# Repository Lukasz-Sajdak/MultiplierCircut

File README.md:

# Multiplier Circuit

## Overview
Analog multiplier circuit designed to perform multiplication of two input signals by utilizing various functional blocks working in tandem. The circuit uses customized components for efficient operation and to meet specific design requirements.

## Main Functional Blocks
The schematic is divided into the following key sections:

### Power Supply
- **Purpose:** Voltage stabilization for the circuit.
- **Components:**
  - **V+ Regulation:** The circuit uses a standard power supply for V+.
  - **V- Generation:** The negative voltage is generated using the **ICL7660AIBAZA** charge pump.

### Charge Pump
- **Purpose:** Generates the negative voltage required for specific circuit components.

### Voltage-Frequency Converter
- **Purpose:** This block, based on the **LM331**, controls and filters the input signal.
- **Adjustment:** The signal can be adjusted using an **R3 potentiometer** for finer control over the frequency.
- **Issue:** The V/F Converter isn't operating as expected due to incorrect resistor choices and insufficient current flowing into the IC.

### Adding Offset
- **Purpose:** Adds a frequency shift to the input signal, ensuring correct operation when dealing with a 0V input.
- **Components:** Implemented with the **TS912** operational amplifier.

### Subtracting Offset
- **Purpose:** Compensates for any voltage offset by subtracting a specific value.
- **Components:** The **TS912** operational amplifier is used here as well, with the offset adjusted via the **R18 potentiometer**.

### Voltage Reference
- **Purpose:** Provides a reference voltage for the circuit.
- **Component:** **TL431BIDBZR** is used for this purpose.

### Analog Switch
- **Component:** **DG419DY**  
- **Purpose:** Transfers charge based on V/F signal to perform multiplication with Vy. Connected to capacitor and output stage.

## How It Works

The circuit receives two input signals: **Vx** and **Vy**, and performs an analog multiplication of these signals.

The **Vx** signal is fed into a voltage-to-frequency converter (**V/F**, based on LM331), which converts the voltage into a frequency proportional to **Vx**. This frequency output is then used to control an analog switch.

The analog switch operates by transferring charge from the **Vy** signal to a capacitor in response to the frequency generated by the V/F converter.

**Switch connections:**
- **IN** — control signal from V/F (frequency depends on **Vx**)  
- **S2** — voltage input **Vy**  
- **D** — capacitor  
- **S1** — output  

As a result, the amount of transferred charge—and thus the output voltage—depends on both the **Vy** amplitude and the frequency determined by **Vx**. This results in **analog multiplication** of **Vx** and **Vy**.

## Known Issues
- The **V/F** is not functioning correctly due to improper resistor selection and insufficient current flow to the integrated circuit. This needs to be addressed for proper operation.

## PCB Design
The physical implementation of the circuit has been designed using **KiCad EDA 8.0.2** software.

The circuit has been **soldered and assembled**.

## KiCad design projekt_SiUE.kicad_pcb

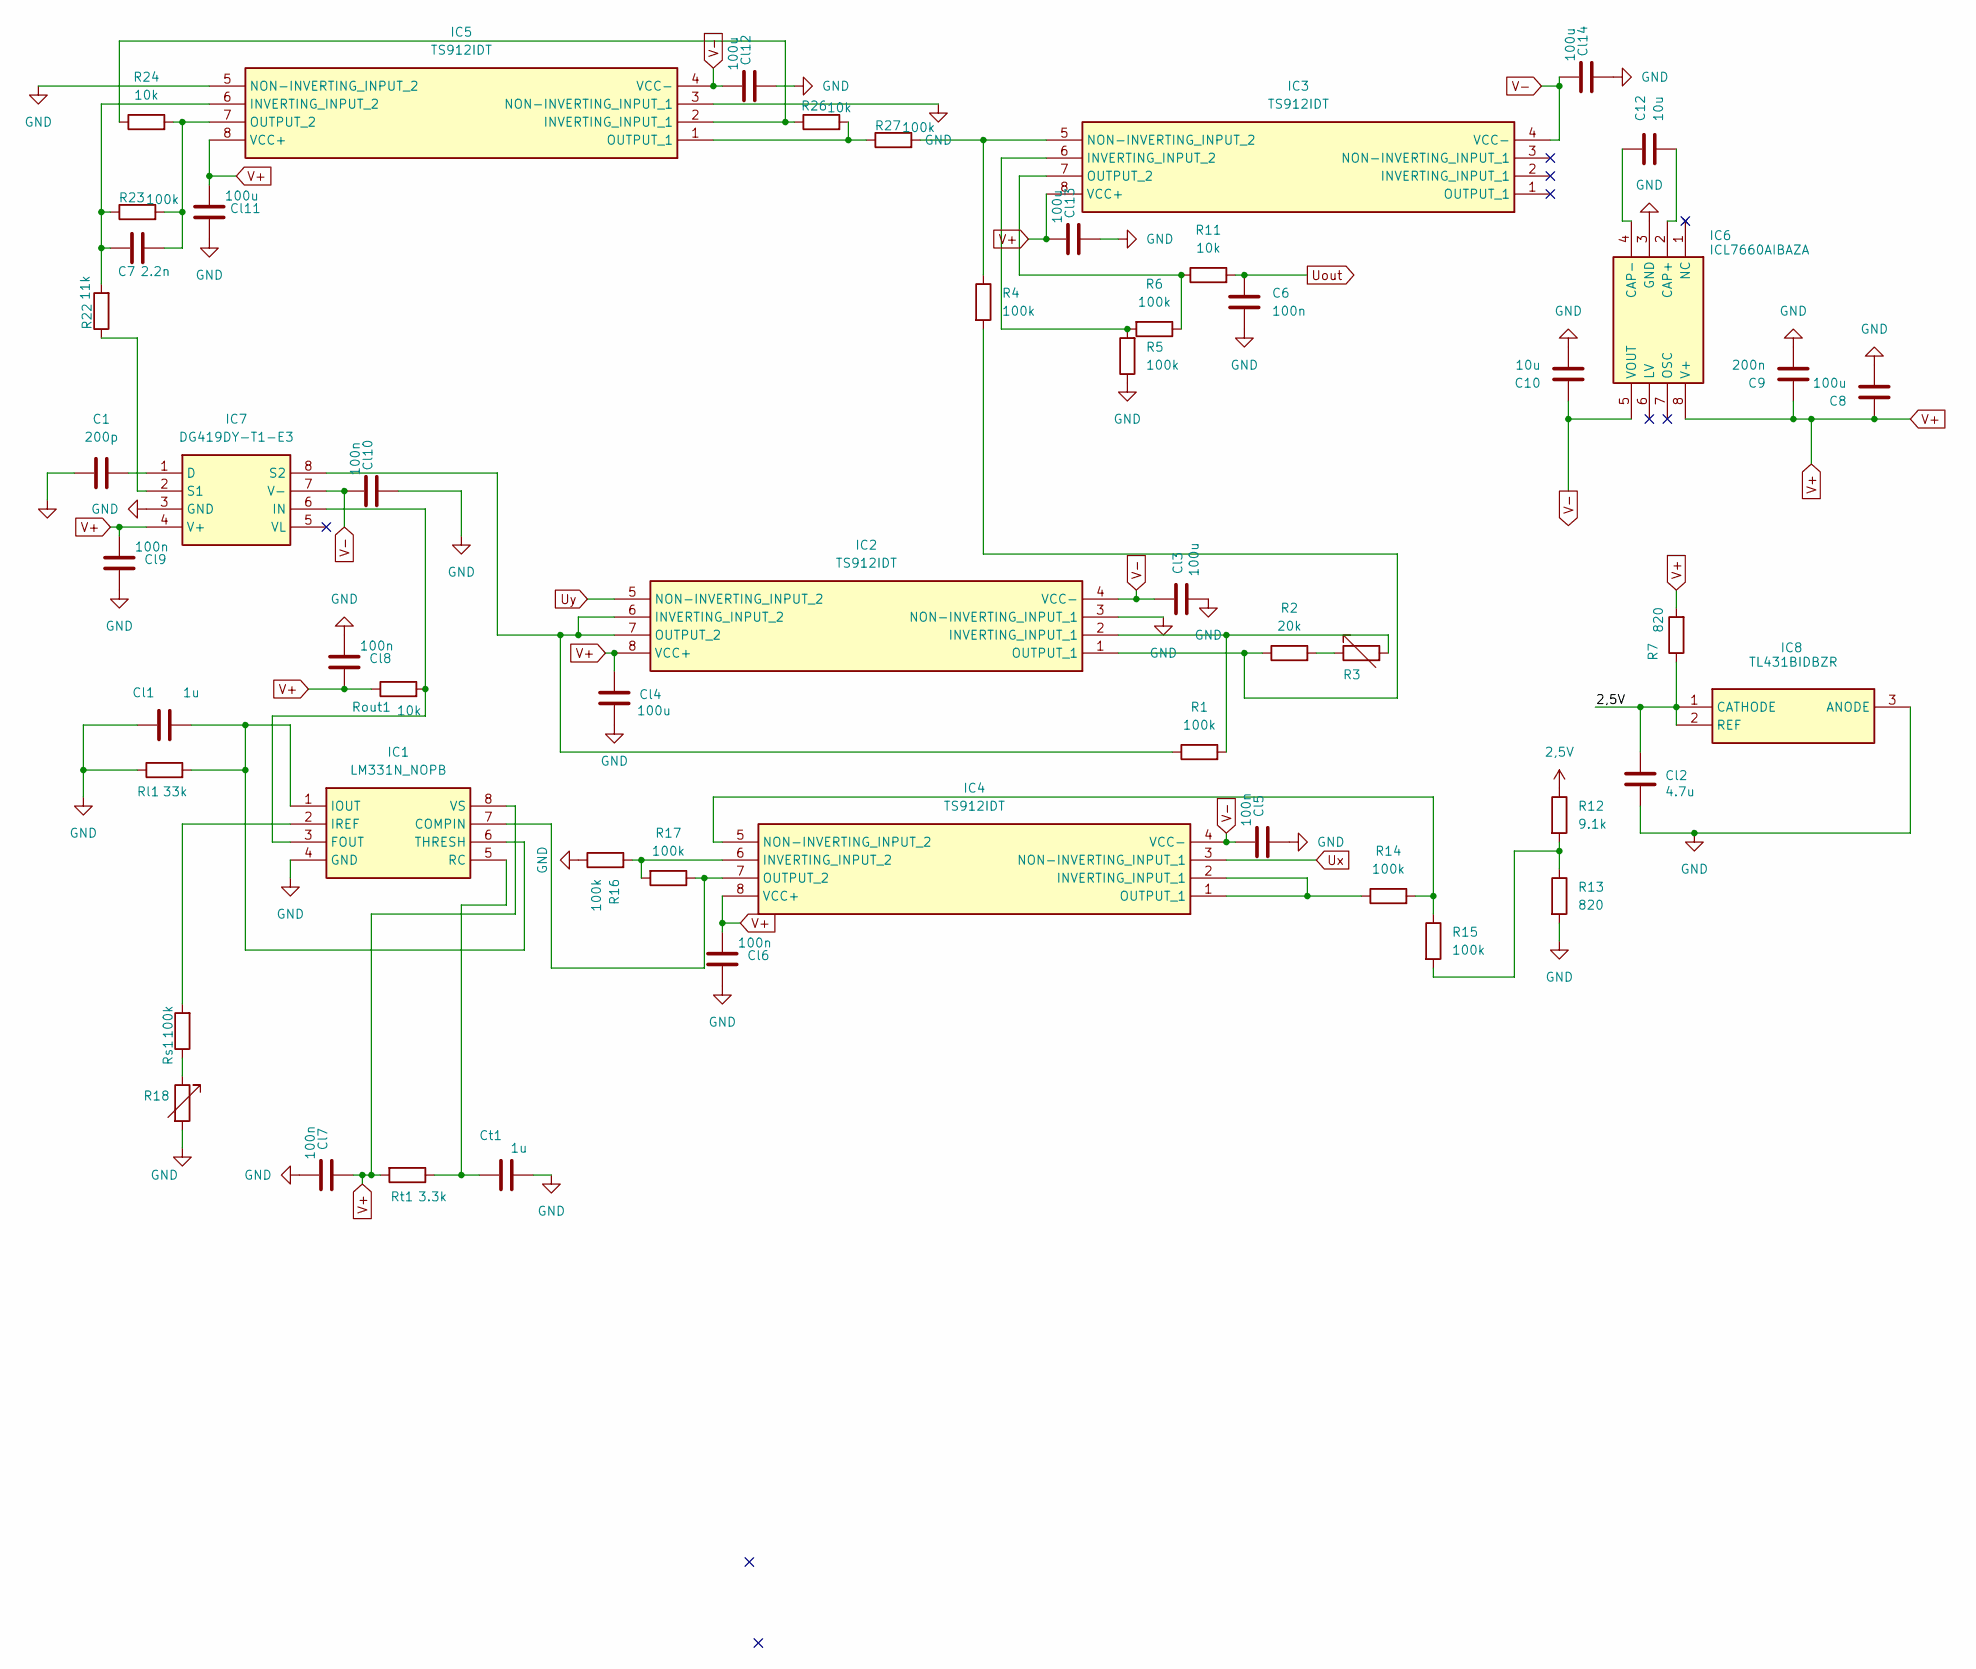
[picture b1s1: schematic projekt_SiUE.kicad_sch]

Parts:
C1: 200p; C_0805_2012Metric_Pad1.18x1.45mm_HandSolder
C6: 100n; C_0805_2012Metric_Pad1.18x1.45mm_HandSolder
C7: 2.2n; C_0805_2012Metric_Pad1.18x1.45mm_HandSolder
C8: 100u; CP_EIA-3528-21_Kemet-B
C9: 200n; C_0805_2012Metric_Pad1.18x1.45mm_HandSolder
C10, C12: 10u; C_0805_2012Metric_Pad1.18x1.45mm_HandSolder
Cl1: 1u; C_0805_2012Metric_Pad1.18x1.45mm_HandSolder
Cl2: 4.7u; C_0805_2012Metric_Pad1.18x1.45mm_HandSolder
Cl3, Cl4, Cl11, Cl12, Cl13, Cl14: 100u; C_0805_2012Metric_Pad1.18x1.45mm_HandSolder
Cl5: 100n; CP_EIA-3528-21_Kemet-B
Cl6, Cl7, Cl8, Cl9, Cl10: 100n; C_0805_2012Metric_Pad1.18x1.45mm_HandSolder
Ct1: 1u; C_0805_2012Metric_Pad1.18x1.45mm_HandSolder
IC1: LM331N_NOPB; DIP794W53P254L959H508Q8N; Manufacturer_Part_Number LM331N/NOPB
IC2, IC3, IC4, IC5: TS912IDT; SOIC127P600X175-8N; Manufacturer_Part_Number TS912IDT
IC6: ICL7660AIBAZA; SOIC127P600X175-8N; Manufacturer_Part_Number ICL7660AIBAZA
IC7: DG419DY-T1-E3; SOIC127P600X175-8N; Manufacturer_Part_Number DG419DY-T1-E3
IC8: TL431BIDBZR; SOT95P237X112-3N; Manufacturer_Part_Number TL431BIDBZR
R1, R4, R5, R6, R14, R15, R16, R17, R23, R27: 100k; R_0805_2012Metric_Pad1.20x1.40mm_HandSolder
R2: 20k; R_0805_2012Metric_Pad1.20x1.40mm_HandSolder
R3, R18: R_Variable; Potentiometer_ACP_CA6-VSMD_Vertical
R7, R13: 820; R_0805_2012Metric_Pad1.20x1.40mm_HandSolder
R11, R24, R26: 10k; R_0805_2012Metric_Pad1.20x1.40mm_HandSolder
R12: 9.1k; R_0805_2012Metric_Pad1.20x1.40mm_HandSolder
R22: 11k; R_0805_2012Metric_Pad1.20x1.40mm_HandSolder
Rl1: 33k; R_0805_2012Metric_Pad1.20x1.40mm_HandSolder
Rout1: 10k; R_0805_2012Metric_Pad1.20x1.40mm_HandSolder
Rs1: 100k; R_0805_2012Metric_Pad1.20x1.40mm_HandSolder
Rt1: 3.3k; R_0805_2012Metric_Pad1.20x1.40mm_HandSolder

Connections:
2,5V: Cl2.2, IC8.1 (CATHODE), IC8.2 (REF), R7.1, R12.1
GND: C1.1, C6.2, C8.2, C9.1, C10.1, Cl1.2, Cl2.1, Cl3.1, Cl4.1, Cl5.1, Cl6.1, Cl7.2, Cl8.2, Cl9.1, Cl10.1, Cl11.1, Cl12.1, Cl13.1, Cl14.1, Ct1.1, IC1.4 (GND), IC2.3 (NON-INVERTING_INPUT_1), IC5.3 (NON-INVERTING_INPUT_1), IC5.5 (NON-INVERTING_INPUT_2), IC6.3 (GND), IC7.3 (GND), IC8.3 (ANODE), R5.1, R13.2, R16.1, R18.2, Rl1.1
unnamed: IC1.7 (COMPIN), IC4.7 (OUTPUT_2), R17.1
unnamed: IC1.3 (FOUT), IC7.6 (IN), Rout1.2
unnamed: Cl1.1, IC1.1 (IOUT), IC1.6 (THRESH), Rl1.2
unnamed: IC1.2 (IREF), Rs1.2
unnamed: Ct1.2, IC1.5 (RC), Rt1.1
unnamed: IC2.2 (INVERTING_INPUT_1), R1.2, R3.2
unnamed: IC2.6 (INVERTING_INPUT_2), IC2.7 (OUTPUT_2), IC7.8 (S2), R1.1
unnamed: IC2.1 (OUTPUT_1), R2.1, R4.2
unnamed: IC3.6 (INVERTING_INPUT_2), R5.2, R6.2
unnamed: IC3.5 (NON-INVERTING_INPUT_2), R4.1, R27.2
unnamed: IC3.7 (OUTPUT_2), R6.1, R11.1
unnamed: IC4.1 (OUTPUT_1), IC4.2 (INVERTING_INPUT_1), R14.1
unnamed: IC4.6 (INVERTING_INPUT_2), R16.2, R17.2
unnamed: IC4.5 (NON-INVERTING_INPUT_2), R14.2, R15.1
unnamed: IC5.2 (INVERTING_INPUT_1), R24.1, R26.1
unnamed: C7.1, IC5.6 (INVERTING_INPUT_2), R22.2, R23.1
unnamed: IC5.1 (OUTPUT_1), R26.2, R27.1
unnamed: C7.2, IC5.7 (OUTPUT_2), R23.2, R24.2
unnamed: C12.1, IC6.2 (CAP+)
unnamed: C12.2, IC6.4 (CAP-)
unnamed: C1.2, IC7.1 (D)
unnamed: IC7.2 (S1), R22.1
unnamed: R2.2, R3.1
unnamed: R12.2, R13.1, R15.2
unnamed: R18.1, Rs1.1
Uout: C6.1, R11.2
Ux: IC4.3 (NON-INVERTING_INPUT_1)
Uy: IC2.5 (NON-INVERTING_INPUT_2)
V+: C8.1, C9.2, Cl4.2, Cl6.2, Cl7.1, Cl8.1, Cl9.2, Cl11.2, Cl13.2, IC1.8 (VS), IC2.8 (VCC+), IC3.8 (VCC+), IC4.8 (VCC+), IC5.8 (VCC+), IC6.8 (V+), IC7.4 (V+), R7.2, Rout1.1, Rt1.2
V-: C10.2, Cl3.2, Cl5.2, Cl10.2, Cl12.2, Cl14.2, IC2.4 (VCC-), IC3.4 (VCC-), IC4.4 (VCC-), IC5.4 (VCC-), IC6.5 (VOUT), IC7.7 (V-)

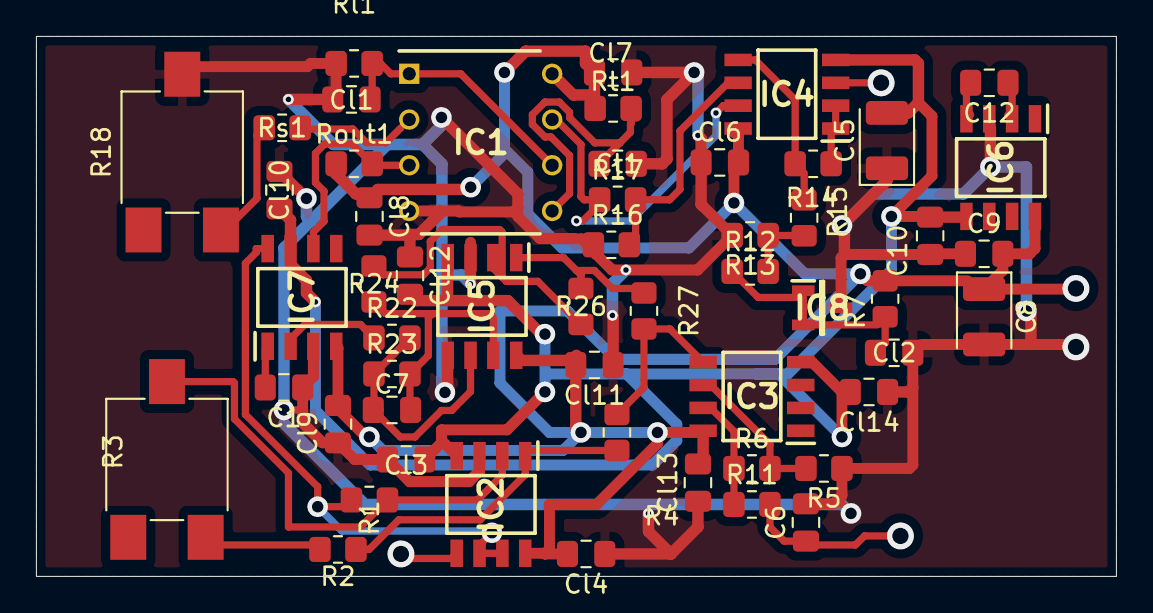
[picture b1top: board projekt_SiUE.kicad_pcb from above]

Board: 2 copper layers, 60.0 x 30.0 mm, 54 parts (0 on the bottom side), 30 nets.
